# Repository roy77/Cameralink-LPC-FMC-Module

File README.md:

Cameralink-LPC-FMC-Module

Eagle_Project
Eagle CAD files of schematics and board layout

Eclipse_Project
C++ Project to control dataflow

Vivado_Project
Source code of zedboard firmware (bitfile)

devicetreeUIO.dts
Source of device tree blob (dtb file)

SD_Card_Image_4GB
image of sd card generated with Win32DiskImager and compressed with 7zip

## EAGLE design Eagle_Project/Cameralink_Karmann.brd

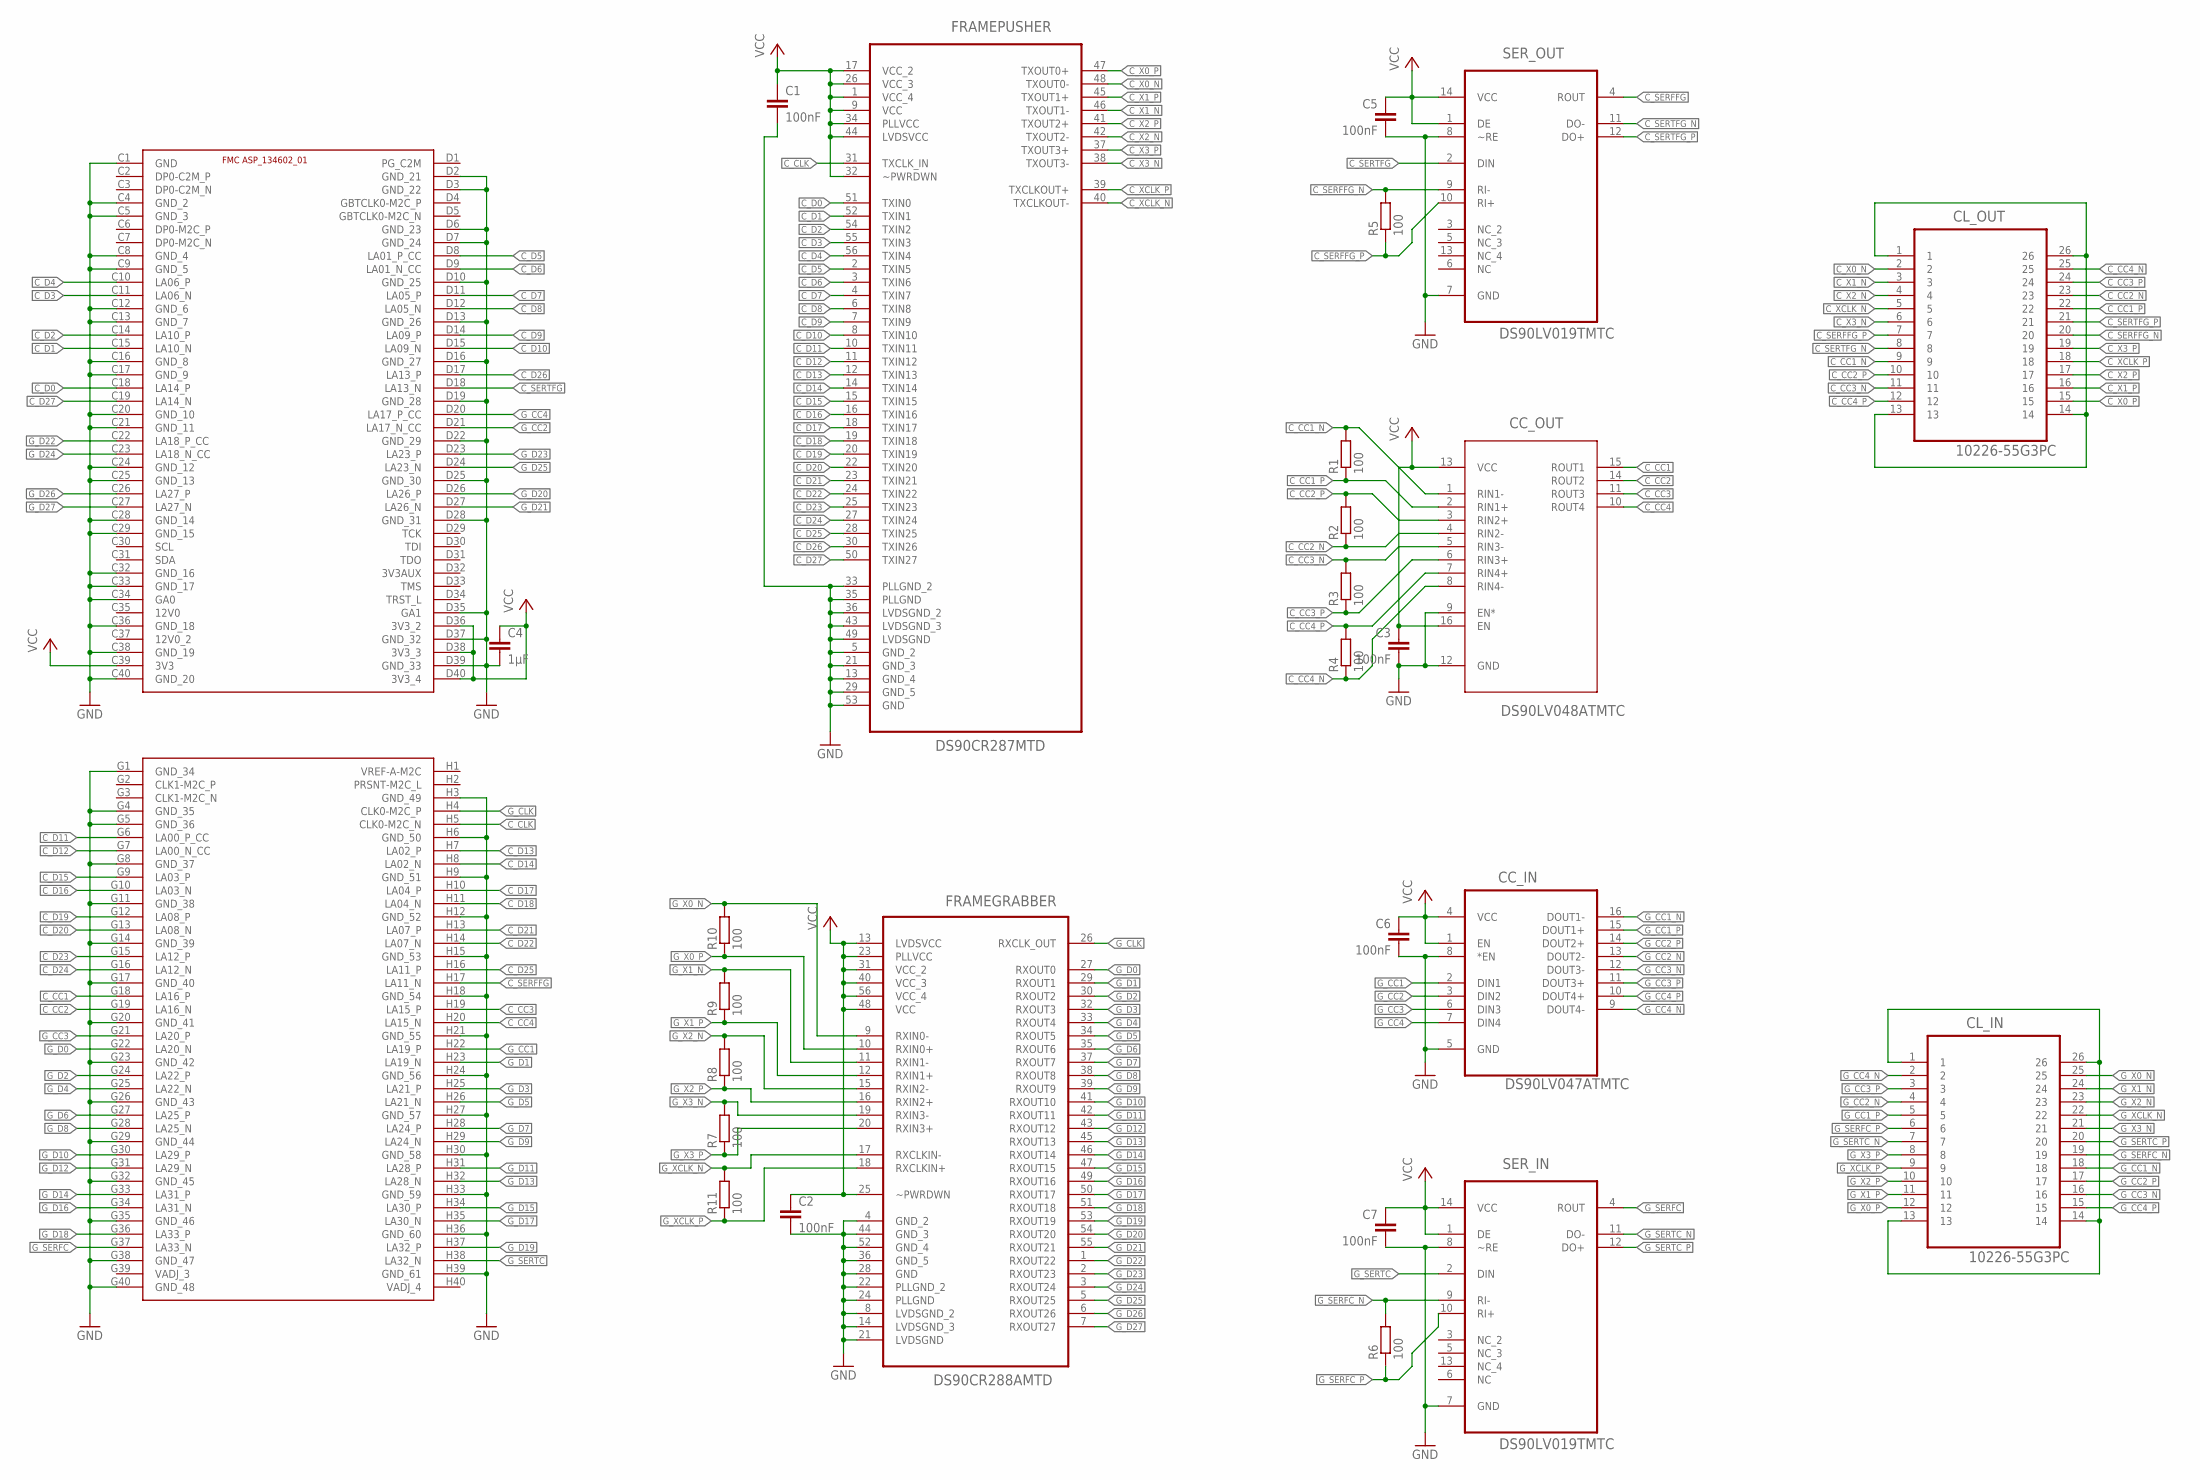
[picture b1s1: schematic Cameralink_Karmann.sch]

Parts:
C1, C2, C3, C5, C6, C7: 100nF; C1206
C4: 1µF; C1206
CC_IN: DS90LV047ATMTC; SOP65P640X110-16N
CC_OUT: DS90LV048ATMTC; SOP65P640X110-16N
CL_IN: 10226-55G3PC; 3M_10226-55G3PC
CL_OUT: 10226-55G3PC; 3M_10226-55G3PC
FRAMEGRABBER: DS90CR288AMTD; SOP50P810X110-56N
FRAMEPUSHER: DS90CR287MTD; SOP50P810X110-56N
R1, R2, R3, R4, R5, R6, R7, R8, R9, R10, R11: 100; R1206
SER_IN: DS90LV019TMTC; SOP65P640X110-14N
SER_OUT: DS90LV019TMTC; SOP65P640X110-14N
U$1: ASP_134602_01

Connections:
C_CC1: CC_OUT.15 (ROUT1), U$1.G18 (LA16_P)
C_CC1_N: CC_OUT.1 (RIN1-), CL_OUT.9, R1.2
C_CC1_P: CC_OUT.2 (RIN1+), CL_OUT.22, R1.1
C_CC2: CC_OUT.14 (ROUT2), U$1.G19 (LA16_N)
C_CC2_N: CC_OUT.4 (RIN2-), CL_OUT.23, R2.1
C_CC2_P: CC_OUT.3 (RIN2+), CL_OUT.10, R2.2
C_CC3: CC_OUT.11 (ROUT3), U$1.H19 (LA15_P)
C_CC3_N: CC_OUT.5 (RIN3-), CL_OUT.11, R3.2
C_CC3_P: CC_OUT.6 (RIN3+), CL_OUT.24, R3.1
C_CC4: CC_OUT.10 (ROUT4), U$1.H20 (LA15_N)
C_CC4_N: CC_OUT.8 (RIN4-), CL_OUT.25, R4.1
C_CC4_P: CC_OUT.7 (RIN4+), CL_OUT.12, R4.2
C_CLK: FRAMEPUSHER.31 (TXCLK_IN), U$1.H5 (CLK0-M2C_N)
C_D0: FRAMEPUSHER.51 (TXIN0), U$1.C18 (LA14_P)
C_D1: FRAMEPUSHER.52 (TXIN1), U$1.C15 (LA10_N)
C_D2: FRAMEPUSHER.54 (TXIN2), U$1.C14 (LA10_P)
C_D3: FRAMEPUSHER.55 (TXIN3), U$1.C11 (LA06_N)
C_D4: FRAMEPUSHER.56 (TXIN4), U$1.C10 (LA06_P)
C_D5: FRAMEPUSHER.2 (TXIN5), U$1.D8 (LA01_P_CC)
C_D6: FRAMEPUSHER.3 (TXIN6), U$1.D9 (LA01_N_CC)
C_D7: FRAMEPUSHER.4 (TXIN7), U$1.D11 (LA05_P)
C_D8: FRAMEPUSHER.6 (TXIN8), U$1.D12 (LA05_N)
C_D9: FRAMEPUSHER.7 (TXIN9), U$1.D14 (LA09_P)
C_D10: FRAMEPUSHER.8 (TXIN10), U$1.D15 (LA09_N)
C_D11: FRAMEPUSHER.10 (TXIN11), U$1.G6 (LA00_P_CC)
C_D12: FRAMEPUSHER.11 (TXIN12), U$1.G7 (LA00_N_CC)
C_D13: FRAMEPUSHER.12 (TXIN13), U$1.H7 (LA02_P)
C_D14: FRAMEPUSHER.14 (TXIN14), U$1.H8 (LA02_N)
C_D15: FRAMEPUSHER.15 (TXIN15), U$1.G9 (LA03_P)
C_D16: FRAMEPUSHER.16 (TXIN16), U$1.G10 (LA03_N)
C_D17: FRAMEPUSHER.18 (TXIN17), U$1.H10 (LA04_P)
C_D18: FRAMEPUSHER.19 (TXIN18), U$1.H11 (LA04_N)
C_D19: FRAMEPUSHER.20 (TXIN19), U$1.G12 (LA08_P)
C_D20: FRAMEPUSHER.22 (TXIN20), U$1.G13 (LA08_N)
C_D21: FRAMEPUSHER.23 (TXIN21), U$1.H13 (LA07_P)
C_D22: FRAMEPUSHER.24 (TXIN22), U$1.H14 (LA07_N)
C_D23: FRAMEPUSHER.25 (TXIN23), U$1.G15 (LA12_P)
C_D24: FRAMEPUSHER.27 (TXIN24), U$1.G16 (LA12_N)
C_D25: FRAMEPUSHER.28 (TXIN25), U$1.H16 (LA11_P)
C_D26: FRAMEPUSHER.30 (TXIN26), U$1.D17 (LA13_P)
C_D27: FRAMEPUSHER.50 (TXIN27), U$1.C19 (LA14_N)
C_SERFFG: SER_OUT.4 (ROUT), U$1.H17 (LA11_N)
C_SERFFG_N: CL_OUT.20, R5.2, SER_OUT.9 (RI-)
C_SERFFG_P: CL_OUT.7, R5.1, SER_OUT.10 (RI+)
C_SERTFG: SER_OUT.2 (DIN), U$1.D18 (LA13_N)
C_SERTFG_N: CL_OUT.8, SER_OUT.11 (DO-)
C_SERTFG_P: CL_OUT.21, SER_OUT.12 (DO+)
C_SHIELD: CL_OUT.1, CL_OUT.13, CL_OUT.14, CL_OUT.26
C_X0_N: CL_OUT.2, FRAMEPUSHER.48 (TXOUT0-)
C_X0_P: CL_OUT.15, FRAMEPUSHER.47 (TXOUT0+)
C_X1_N: CL_OUT.3, FRAMEPUSHER.46 (TXOUT1-)
C_X1_P: CL_OUT.16, FRAMEPUSHER.45 (TXOUT1+)
C_X2_N: CL_OUT.4, FRAMEPUSHER.42 (TXOUT2-)
C_X2_P: CL_OUT.17, FRAMEPUSHER.41 (TXOUT2+)
C_X3_N: CL_OUT.6, FRAMEPUSHER.38 (TXOUT3-)
C_X3_P: CL_OUT.19, FRAMEPUSHER.37 (TXOUT3+)
C_XCLK_N: CL_OUT.5, FRAMEPUSHER.40 (TXCLKOUT-)
C_XCLK_P: CL_OUT.18, FRAMEPUSHER.39 (TXCLKOUT+)
GND: C1.2, C2.2, C3.2, C4.2, C5.2, C6.2, C7.2, CC_IN.5 (GND), CC_IN.8 (*EN), CC_OUT.9 (EN*), CC_OUT.12 (GND), FRAMEGRABBER.4 (GND_2), FRAMEGRABBER.8 (LVDSGND_2), FRAMEGRABBER.14 (LVDSGND_3), FRAMEGRABBER.21 (LVDSGND), FRAMEGRABBER.22 (PLLGND_2), FRAMEGRABBER.24 (PLLGND), FRAMEGRABBER.28 (GND), FRAMEGRABBER.36 (GND_5), FRAMEGRABBER.44 (GND_3), FRAMEGRABBER.52 (GND_4), FRAMEPUSHER.5 (GND_2), FRAMEPUSHER.13 (GND_4), FRAMEPUSHER.21 (GND_3), FRAMEPUSHER.29 (GND_5), FRAMEPUSHER.33 (PLLGND_2), FRAMEPUSHER.35 (PLLGND), FRAMEPUSHER.36 (LVDSGND_2), FRAMEPUSHER.43 (LVDSGND_3), FRAMEPUSHER.49 (LVDSGND), FRAMEPUSHER.53 (GND), SER_IN.7 (GND), SER_IN.8 (~RE), SER_OUT.7 (GND), SER_OUT.8 (~RE), U$1.C1 (GND), U$1.C4 (GND_2), U$1.C5 (GND_3), U$1.C8 (GND_4), U$1.C9 (GND_5), U$1.C12 (GND_6), U$1.C13 (GND_7), U$1.C16 (GND_8), U$1.C17 (GND_9), U$1.C20 (GND_10), U$1.C21 (GND_11), U$1.C24 (GND_12), U$1.C25 (GND_13), U$1.C28 (GND_14), U$1.C29 (GND_15), U$1.C32 (GND_16), U$1.C33 (GND_17), U$1.C34 (GA0), U$1.C36 (GND_18), U$1.C38 (GND_19), U$1.C40 (GND_20), U$1.D2 (GND_21), U$1.D3 (GND_22), U$1.D6 (GND_23), U$1.D7 (GND_24), U$1.D10 (GND_25), U$1.D13 (GND_26), U$1.D16 (GND_27), U$1.D19 (GND_28), U$1.D22 (GND_29), U$1.D25 (GND_30), U$1.D28 (GND_31), U$1.D35 (GA1), U$1.D37 (GND_32), U$1.D39 (GND_33), U$1.G1 (GND_34), U$1.G4 (GND_35), U$1.G5 (GND_36), U$1.G8 (GND_37), U$1.G11 (GND_38), U$1.G14 (GND_39), U$1.G17 (GND_40), U$1.G20 (GND_41), U$1.G23 (GND_42), U$1.G26 (GND_43), U$1.G29 (GND_44), U$1.G32 (GND_45), U$1.G35 (GND_46), U$1.G38 (GND_47), U$1.G40 (GND_48), U$1.H3 (GND_49), U$1.H6 (GND_50), U$1.H9 (GND_51), U$1.H12 (GND_52), U$1.H15 (GND_53), U$1.H18 (GND_54), U$1.H21 (GND_55), U$1.H24 (GND_56), U$1.H27 (GND_57), U$1.H30 (GND_58), U$1.H33 (GND_59), U$1.H36 (GND_60), U$1.H39 (GND_61)
G_CC1: CC_IN.2 (DIN1), U$1.H22 (LA19_P)
G_CC1_N: CC_IN.16 (DOUT1-), CL_IN.18
G_CC1_P: CC_IN.15 (DOUT1+), CL_IN.5
G_CC2: CC_IN.3 (DIN2), U$1.D21 (LA17_N_CC)
G_CC2_N: CC_IN.13 (DOUT2-), CL_IN.4
G_CC2_P: CC_IN.14 (DOUT2+), CL_IN.17
G_CC3: CC_IN.6 (DIN3), U$1.G21 (LA20_P)
G_CC3_N: CC_IN.12 (DOUT3-), CL_IN.16
G_CC3_P: CC_IN.11 (DOUT3+), CL_IN.3
G_CC4: CC_IN.7 (DIN4), U$1.D20 (LA17_P_CC)
G_CC4_N: CC_IN.9 (DOUT4-), CL_IN.2
G_CC4_P: CC_IN.10 (DOUT4+), CL_IN.15
G_CLK: FRAMEGRABBER.26 (RXCLK_OUT), U$1.H4 (CLK0-M2C_P)
G_D0: FRAMEGRABBER.27 (RXOUT0), U$1.G22 (LA20_N)
G_D1: FRAMEGRABBER.29 (RXOUT1), U$1.H23 (LA19_N)
G_D2: FRAMEGRABBER.30 (RXOUT2), U$1.G24 (LA22_P)
G_D3: FRAMEGRABBER.32 (RXOUT3), U$1.H25 (LA21_P)
G_D4: FRAMEGRABBER.33 (RXOUT4), U$1.G25 (LA22_N)
G_D5: FRAMEGRABBER.34 (RXOUT5), U$1.H26 (LA21_N)
G_D6: FRAMEGRABBER.35 (RXOUT6), U$1.G27 (LA25_P)
G_D7: FRAMEGRABBER.37 (RXOUT7), U$1.H28 (LA24_P)
G_D8: FRAMEGRABBER.38 (RXOUT8), U$1.G28 (LA25_N)
G_D9: FRAMEGRABBER.39 (RXOUT9), U$1.H29 (LA24_N)
G_D10: FRAMEGRABBER.41 (RXOUT10), U$1.G30 (LA29_P)
G_D11: FRAMEGRABBER.42 (RXOUT11), U$1.H31 (LA28_P)
G_D12: FRAMEGRABBER.43 (RXOUT12), U$1.G31 (LA29_N)
G_D13: FRAMEGRABBER.45 (RXOUT13), U$1.H32 (LA28_N)
G_D14: FRAMEGRABBER.46 (RXOUT14), U$1.G33 (LA31_P)
G_D15: FRAMEGRABBER.47 (RXOUT15), U$1.H34 (LA30_P)
G_D16: FRAMEGRABBER.49 (RXOUT16), U$1.G34 (LA31_N)
G_D17: FRAMEGRABBER.50 (RXOUT17), U$1.H35 (LA30_N)
G_D18: FRAMEGRABBER.51 (RXOUT18), U$1.G36 (LA33_P)
G_D19: FRAMEGRABBER.53 (RXOUT19), U$1.H37 (LA32_P)
G_D20: FRAMEGRABBER.54 (RXOUT20), U$1.D26 (LA26_P)
G_D21: FRAMEGRABBER.55 (RXOUT21), U$1.D27 (LA26_N)
G_D22: FRAMEGRABBER.1 (RXOUT22), U$1.C22 (LA18_P_CC)
G_D23: FRAMEGRABBER.2 (RXOUT23), U$1.D23 (LA23_P)
G_D24: FRAMEGRABBER.3 (RXOUT24), U$1.C23 (LA18_N_CC)
G_D25: FRAMEGRABBER.5 (RXOUT25), U$1.D24 (LA23_N)
G_D26: FRAMEGRABBER.6 (RXOUT26), U$1.C26 (LA27_P)
G_D27: FRAMEGRABBER.7 (RXOUT27), U$1.C27 (LA27_N)
G_SERFC: SER_IN.4 (ROUT), U$1.G37 (LA33_N)
G_SERFC_N: CL_IN.19, R6.2, SER_IN.9 (RI-)
G_SERFC_P: CL_IN.6, R6.1, SER_IN.10 (RI+)
G_SERTC: SER_IN.2 (DIN), U$1.H38 (LA32_N)
G_SERTC_N: CL_IN.7, SER_IN.11 (DO-)
G_SERTC_P: CL_IN.20, SER_IN.12 (DO+)
G_SHIELD: CL_IN.1, CL_IN.13, CL_IN.14, CL_IN.26
G_X0_N: CL_IN.25, FRAMEGRABBER.9 (RXIN0-), R10.2
G_X0_P: CL_IN.12, FRAMEGRABBER.10 (RXIN0+), R10.1
G_X1_N: CL_IN.24, FRAMEGRABBER.11 (RXIN1-), R9.2
G_X1_P: CL_IN.11, FRAMEGRABBER.12 (RXIN1+), R9.1
G_X2_N: CL_IN.23, FRAMEGRABBER.15 (RXIN2-), R8.2
G_X2_P: CL_IN.10, FRAMEGRABBER.16 (RXIN2+), R8.1
G_X3_N: CL_IN.21, FRAMEGRABBER.19 (RXIN3-), R7.2
G_X3_P: CL_IN.8, FRAMEGRABBER.20 (RXIN3+), R7.1
G_XCLK_N: CL_IN.22, FRAMEGRABBER.17 (RXCLKIN-), R11.2
G_XCLK_P: CL_IN.9, FRAMEGRABBER.18 (RXCLKIN+), R11.1
VCC: C1.1, C2.1, C3.1, C4.1, C5.1, C6.1, C7.1, CC_IN.1 (EN), CC_IN.4 (VCC), CC_OUT.13 (VCC), CC_OUT.16 (EN), FRAMEGRABBER.13 (LVDSVCC), FRAMEGRABBER.23 (PLLVCC), FRAMEGRABBER.25 (~PWRDWN), FRAMEGRABBER.31 (VCC_2), FRAMEGRABBER.40 (VCC_3), FRAMEGRABBER.48 (VCC), FRAMEGRABBER.56 (VCC_4), FRAMEPUSHER.1 (VCC_4), FRAMEPUSHER.9 (VCC), FRAMEPUSHER.17 (VCC_2), FRAMEPUSHER.26 (VCC_3), FRAMEPUSHER.32 (~PWRDWN), FRAMEPUSHER.34 (PLLVCC), FRAMEPUSHER.44 (LVDSVCC), SER_IN.1 (DE), SER_IN.14 (VCC), SER_OUT.1 (DE), SER_OUT.14 (VCC), U$1.C39 (3V3), U$1.D36 (3V3_2), U$1.D38 (3V3_3), U$1.D40 (3V3_4)

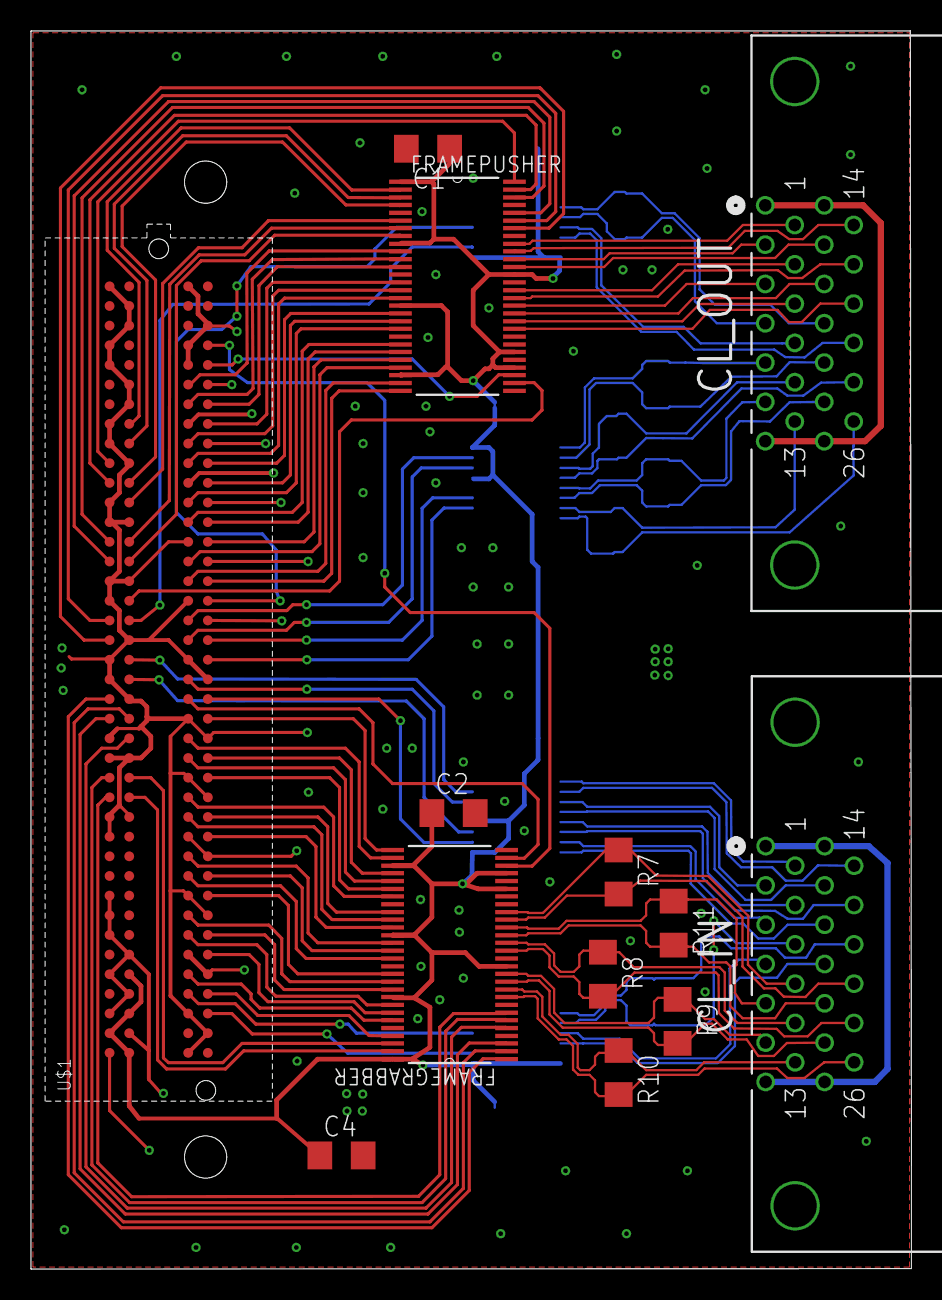
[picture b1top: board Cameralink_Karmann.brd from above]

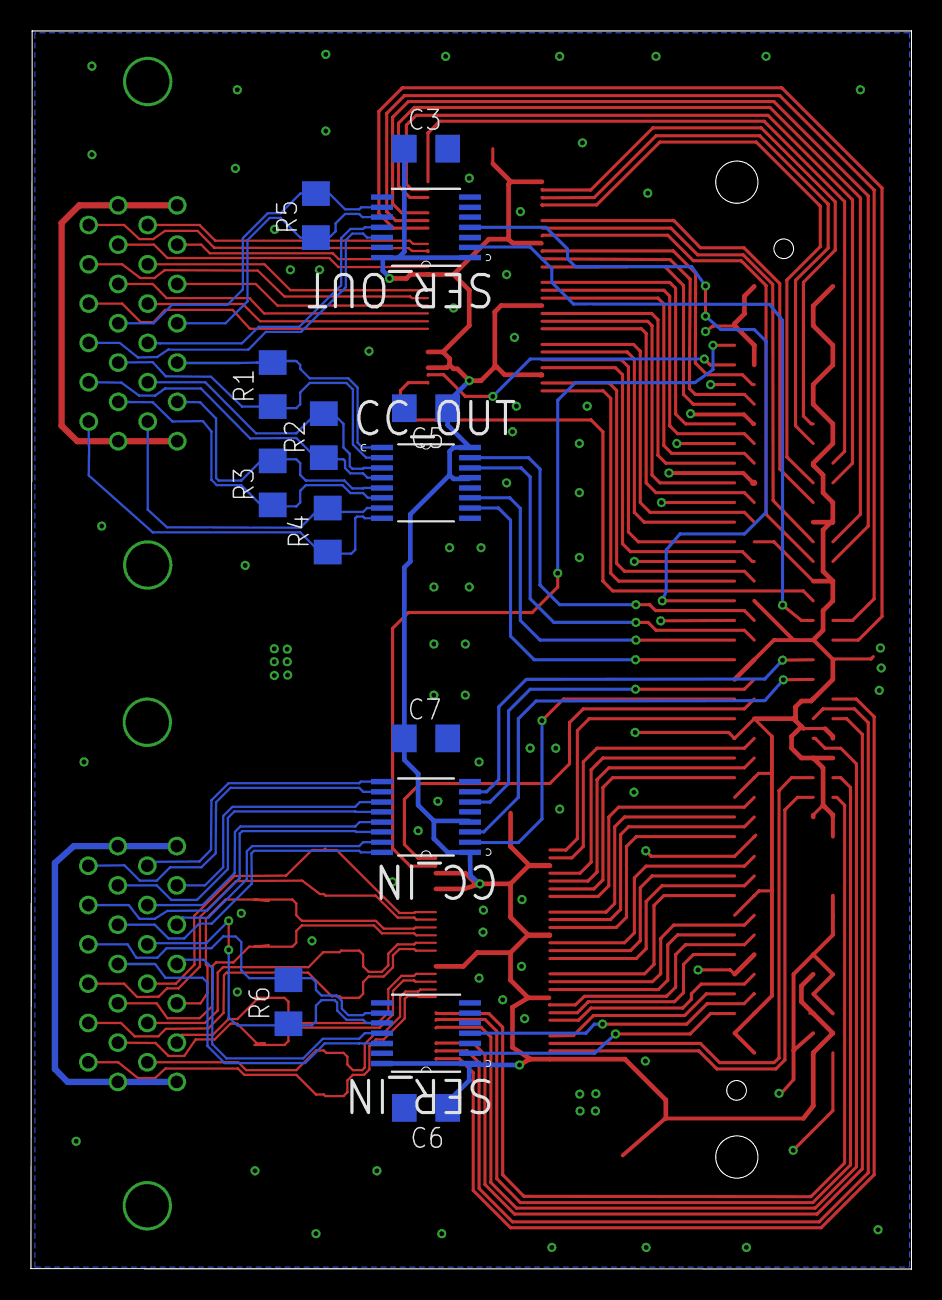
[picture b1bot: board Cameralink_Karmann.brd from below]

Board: 2 copper layers, 56.9 x 80.0 mm, 27 parts (14 on the bottom side), 118 nets.

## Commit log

2015-05-24 second commit
